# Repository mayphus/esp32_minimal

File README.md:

# Minimal ESP32-S3 Board

> **Status:** Hardware snapshot — preserved for reference and not actively maintained.

my esp32-s3-wroom-1 minimal design.

with just,

- esp32-s3-wroom-1
- usb c
- some optional capacitors. (yes, optional, I just confirmed.)

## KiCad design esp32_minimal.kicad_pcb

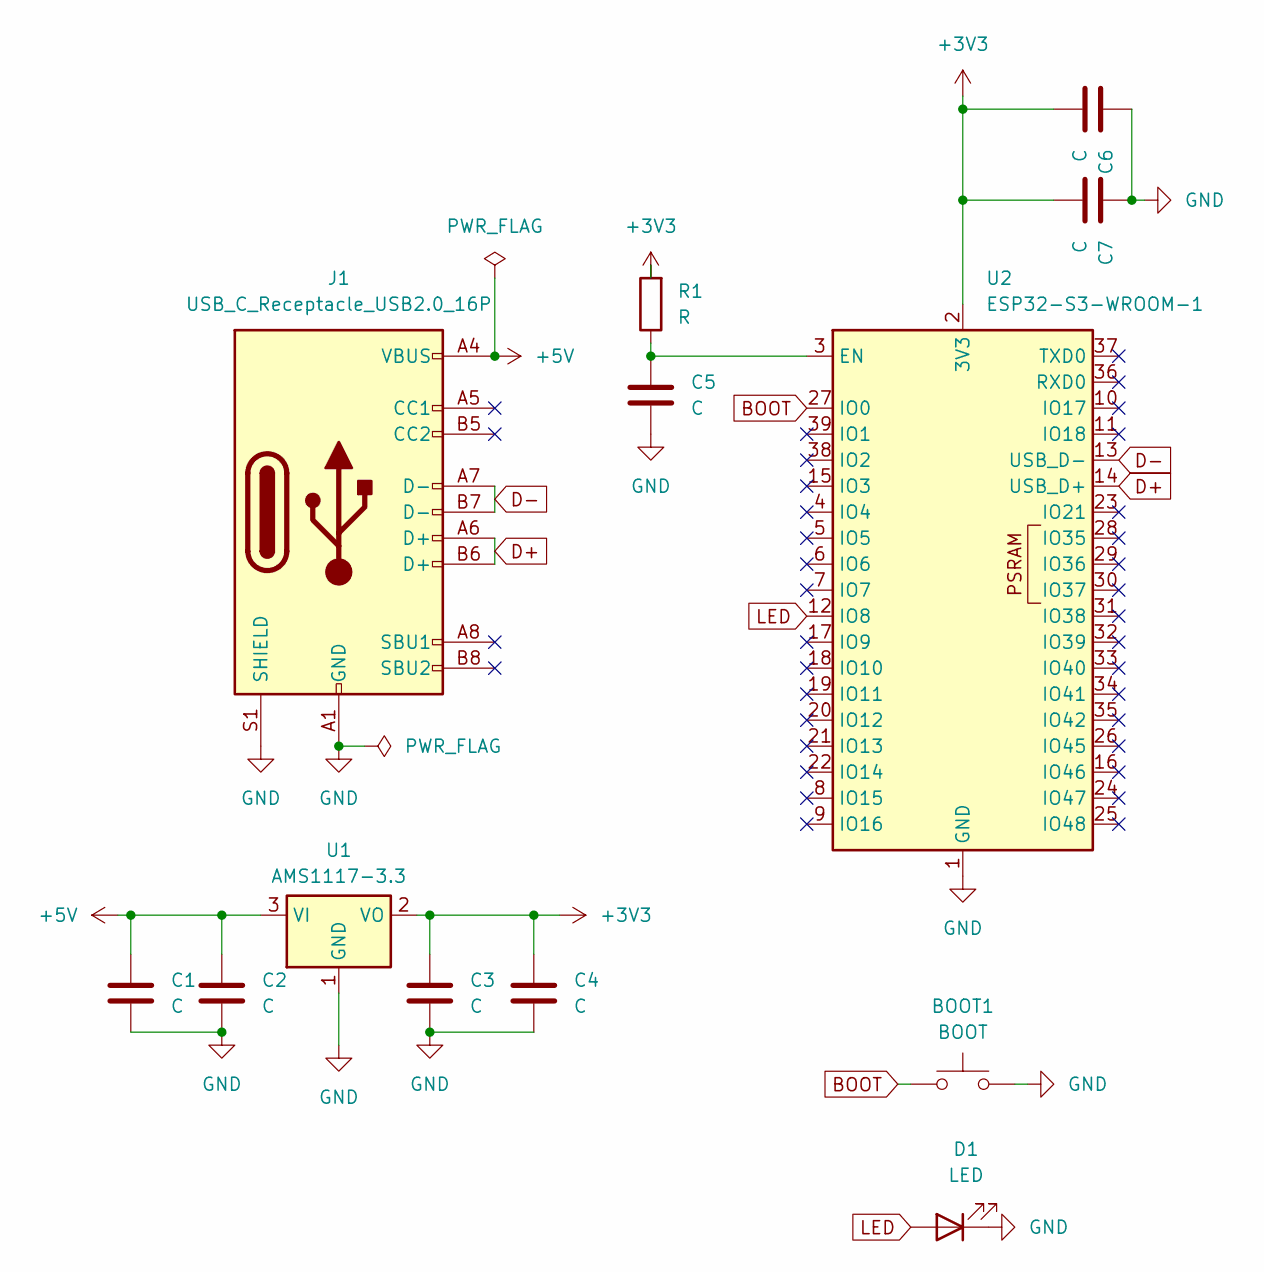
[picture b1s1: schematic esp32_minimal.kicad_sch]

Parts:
BOOT1: BOOT; SW_Push_1P1T_NO_CK_KMR2
C1, C2, C3, C4, C5, C6, C7: C; C_0805_2012Metric
D1: LED; LED_0603_1608Metric
J1: USB_C_Receptacle_USB2.0_16P; USB_C_Receptacle_GCT_USB4105-xx-A_16P_TopMnt_Horizontal
R1: R; R_0805_2012Metric
U1: AMS1117-3.3; SOT-223-3_TabPin2
U2: ESP32-S3-WROOM-1

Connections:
+3V3: C3.1, C4.1, C6.2, C7.2, R1.2, U1.2 (VO), U2.2 (3V3)
+5V: C1.1, C2.1, J1.A4 (VBUS), J1.A9 (VBUS), J1.B4 (VBUS), J1.B9 (VBUS), U1.3 (VI)
BOOT: BOOT1.1, U2.27 (IO0)
D+: J1.A6 (D+), J1.B6 (D+), U2.14 (USB_D+)
D-: J1.A7 (D-), J1.B7 (D-), U2.13 (USB_D-)
GND: BOOT1.2, C1.2, C2.2, C3.2, C4.2, C5.2, C6.1, C7.1, D1.1 (K), J1.A1 (GND), J1.A12 (GND), J1.B1 (GND), J1.B12 (GND), J1.S1 (SHIELD), U1.1 (GND), U2.1 (GND), U2.40 (GND), U2.41 (GND)
LED: D1.2 (A), U2.12 (IO8)
unnamed: C5.1, R1.1, U2.3 (EN)

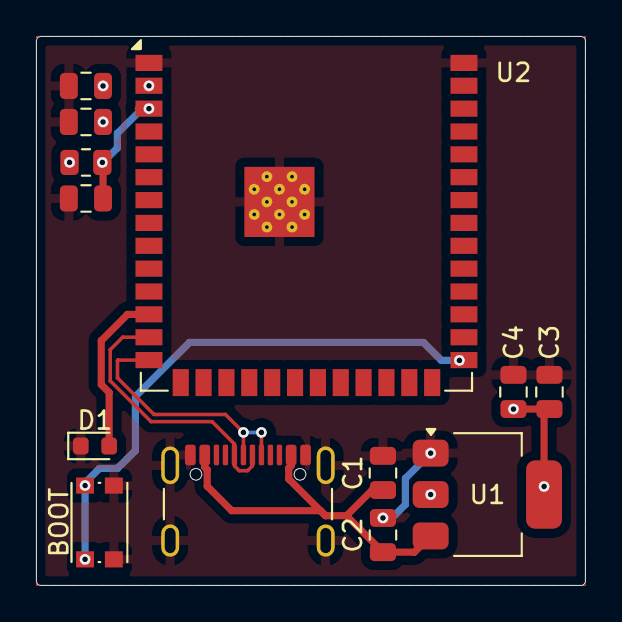
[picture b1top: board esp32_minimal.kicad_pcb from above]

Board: 2 copper layers, 30.5 x 30.5 mm, 13 parts (0 on the bottom side), 8 nets.

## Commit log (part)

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2025-02-15 Initial
